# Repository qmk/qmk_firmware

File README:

To build:

make iris/rev2:pogues_uk

to then install:

make iris/rev2:pogues_uk:avrdude

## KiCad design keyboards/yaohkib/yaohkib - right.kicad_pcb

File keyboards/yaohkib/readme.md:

# YAOHKIB
A custom 42 Key Keyboard.
> - stick out thumb cluster.
> - multiple aux socket locations.
> - 128x64 OLED and 128x32 OLED Support

Keyboard Maintainer: [jabbato](https://github.com/jabbato/)  
Hardware Supported: Pro Micro, 128x64/128x32 OLED
Hardware Availability: [PCB & Case Data](https://github.com/jabbato/yaohkib)

Make example:

```sh
make yaohkib:default
```

See the [build environment setup](https://docs.qmk.fm/#/getting_started_build_tools) and the [make instructions](https://docs.qmk.fm/#/getting_started_make_guide) for more information. Brand new to QMK? Start with our [Complete Newbs Guide](https://docs.qmk.fm/#/newbs).

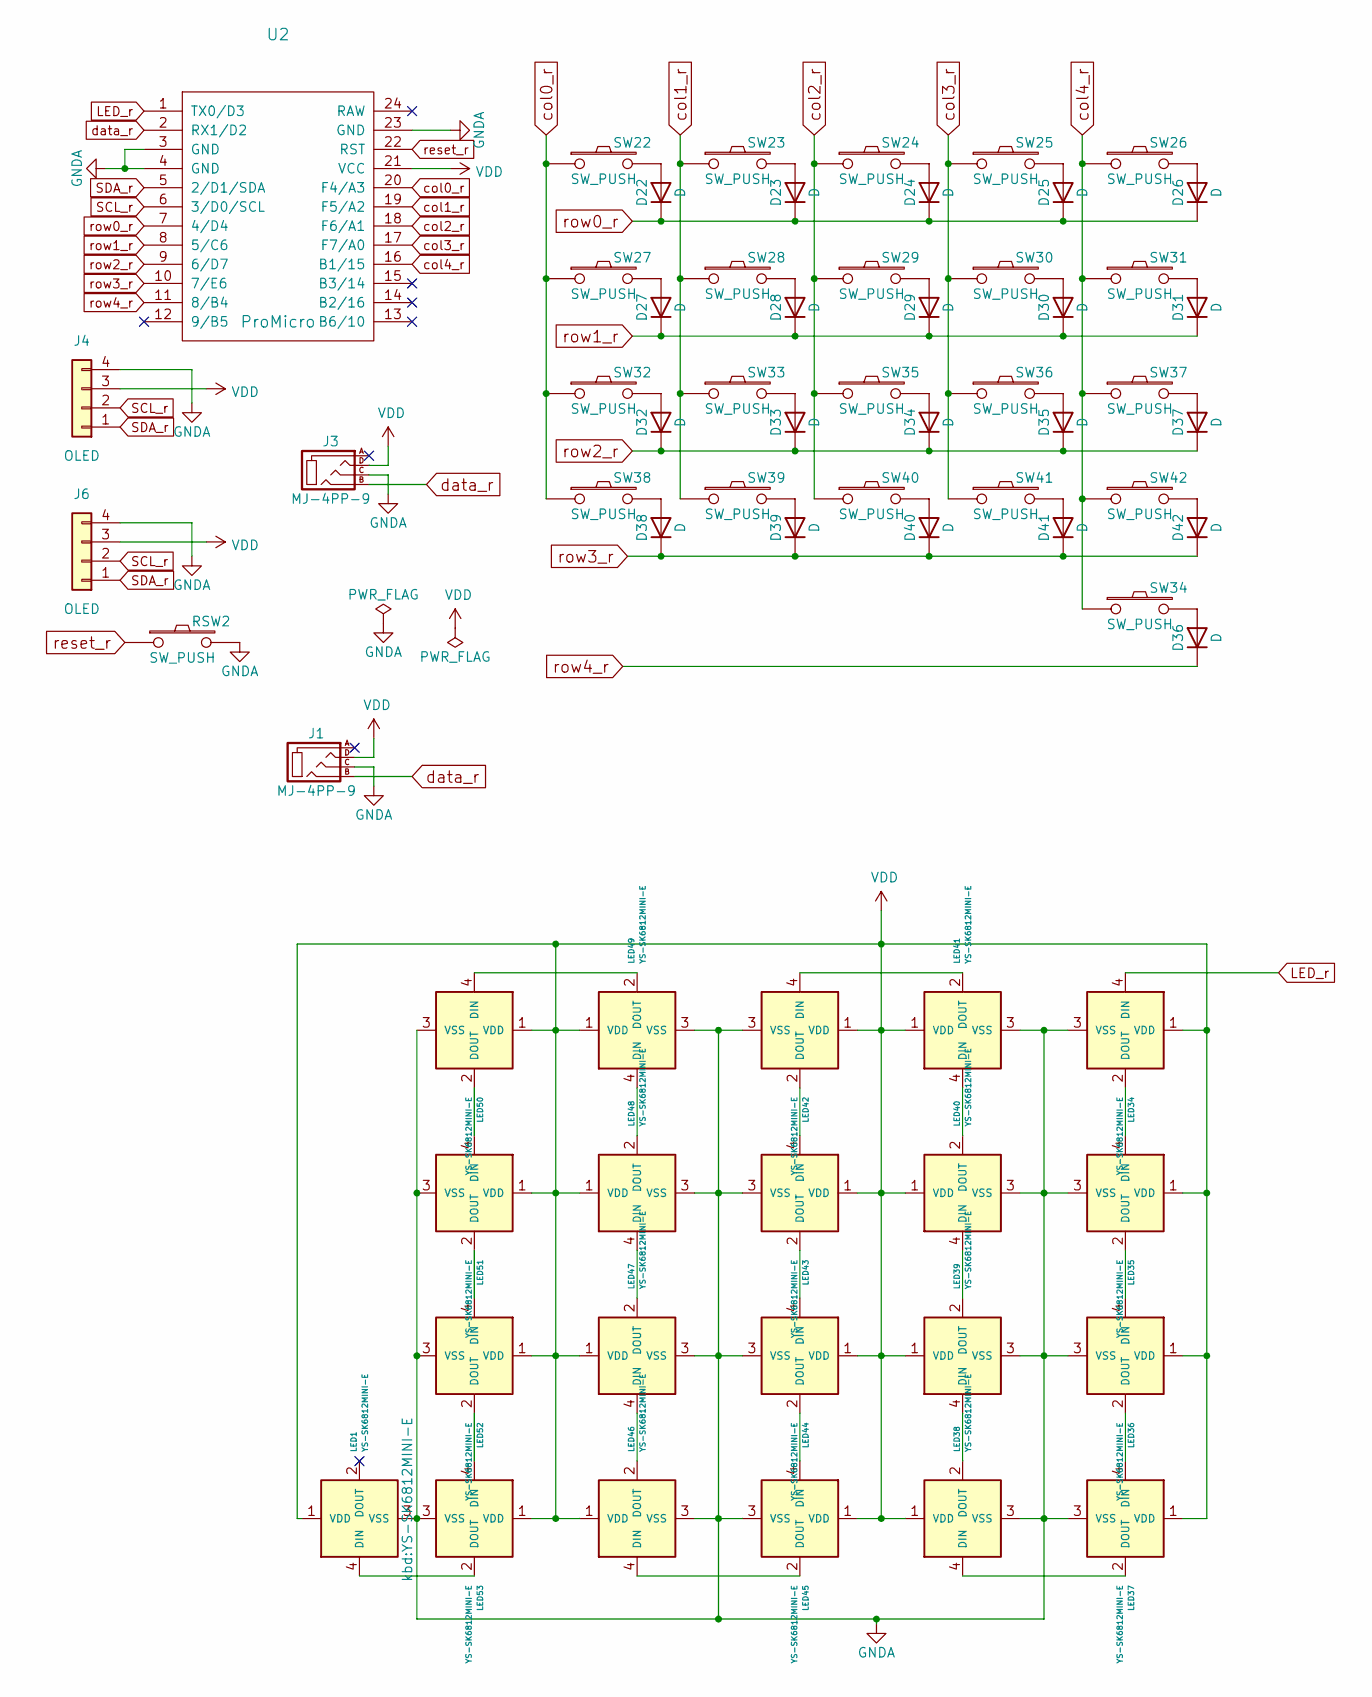
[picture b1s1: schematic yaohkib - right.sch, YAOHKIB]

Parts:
D22, D23, D24, D25, D26, D27, D28, D29, D30, D31, D32, D33, D34, D35, D36, D37, D38, D39, D40, D41, D42: D; D3_SMD_v2
J1, J3: MJ-4PP-9; MJ-4PP-9_1side
J4, J6: OLED; OLED_1side
LED1, LED34, LED35, LED36, LED37, LED38, LED39, LED40, LED41, LED42, LED43, LED44, LED45, LED46, LED47, LED48, LED49, LED50, LED51, LED52, LED53: YS-SK6812MINI-E
RSW2: SW_PUSH; ResetSW_1side
SW22, SW23, SW24, SW25, SW26, SW27, SW28, SW29, SW30, SW31, SW32, SW33, SW35, SW36, SW37, SW38, SW39, SW40: SW_PUSH; CherryMX_Hotswap
SW34, SW41, SW42: SW_PUSH; CherryMX_Hotswap_1.5u
U2: ProMicro; ProMicro_v3

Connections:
GNDA: J1.C, J3.C, J4.4, J6.4, LED1.3 (VSS), LED34.3 (VSS), LED35.3 (VSS), LED36.3 (VSS), LED37.3 (VSS), LED38.3 (VSS), LED39.3 (VSS), LED40.3 (VSS), LED41.3 (VSS), LED42.3 (VSS), LED43.3 (VSS), LED44.3 (VSS), LED45.3 (VSS), LED46.3 (VSS), LED47.3 (VSS), LED48.3 (VSS), LED49.3 (VSS), LED50.3 (VSS), LED51.3 (VSS), LED52.3 (VSS), LED53.3 (VSS), RSW2.2, U2.3 (GND), U2.4 (GND), U2.23 (GND)
LED_r: LED34.4 (DIN), U2.1 (TX0/D3)
unnamed: D22.2 (A), SW22.2
unnamed: D23.2 (A), SW23.2
unnamed: D24.2 (A), SW24.2
unnamed: D25.2 (A), SW25.2
unnamed: D26.2 (A), SW26.2
unnamed: D27.2 (A), SW27.2
unnamed: D28.2 (A), SW28.2
unnamed: D29.2 (A), SW29.2
unnamed: D30.2 (A), SW30.2
unnamed: D31.2 (A), SW31.2
unnamed: D32.2 (A), SW32.2
unnamed: D33.2 (A), SW33.2
unnamed: D34.2 (A), SW35.2
unnamed: D35.2 (A), SW36.2
unnamed: D36.2 (A), SW34.2
unnamed: D37.2 (A), SW37.2
unnamed: D38.2 (A), SW38.2
unnamed: D39.2 (A), SW39.2
unnamed: D40.2 (A), SW40.2
unnamed: D41.2 (A), SW41.2
unnamed: D42.2 (A), SW42.2
unnamed: LED1.4 (DIN), LED53.2 (DOUT)
unnamed: LED34.2 (DOUT), LED35.4 (DIN)
unnamed: LED35.2 (DOUT), LED36.4 (DIN)
unnamed: LED36.2 (DOUT), LED37.4 (DIN)
unnamed: LED37.2 (DOUT), LED38.4 (DIN)
unnamed: LED38.2 (DOUT), LED39.4 (DIN)
unnamed: LED39.2 (DOUT), LED40.4 (DIN)
unnamed: LED40.2 (DOUT), LED41.4 (DIN)
unnamed: LED41.2 (DOUT), LED42.4 (DIN)
unnamed: LED42.2 (DOUT), LED43.4 (DIN)
unnamed: LED43.2 (DOUT), LED44.4 (DIN)
unnamed: LED44.2 (DOUT), LED45.4 (DIN)
unnamed: LED45.2 (DOUT), LED46.4 (DIN)
unnamed: LED46.2 (DOUT), LED47.4 (DIN)
unnamed: LED47.2 (DOUT), LED48.4 (DIN)
unnamed: LED48.2 (DOUT), LED49.4 (DIN)
unnamed: LED49.2 (DOUT), LED50.4 (DIN)
unnamed: LED50.2 (DOUT), LED51.4 (DIN)
unnamed: LED51.2 (DOUT), LED52.4 (DIN)
unnamed: LED52.2 (DOUT), LED53.4 (DIN)
SCL_r: J4.2, J6.2, U2.6 (3/D0/SCL)
SDA_r: J4.1, J6.1, U2.5 (2/D1/SDA)
VDD: J1.D, J3.D, J4.3, J6.3, LED1.1 (VDD), LED34.1 (VDD), LED35.1 (VDD), LED36.1 (VDD), LED37.1 (VDD), LED38.1 (VDD), LED39.1 (VDD), LED40.1 (VDD), LED41.1 (VDD), LED42.1 (VDD), LED43.1 (VDD), LED44.1 (VDD), LED45.1 (VDD), LED46.1 (VDD), LED47.1 (VDD), LED48.1 (VDD), LED49.1 (VDD), LED50.1 (VDD), LED51.1 (VDD), LED52.1 (VDD), LED53.1 (VDD), U2.21 (VCC)
col0_r: SW22.1, SW27.1, SW32.1, SW38.1, U2.20 (F4/A3)
col1_r: SW23.1, SW28.1, SW33.1, SW39.1, U2.19 (F5/A2)
col2_r: SW24.1, SW29.1, SW35.1, SW40.1, U2.18 (F6/A1)
col3_r: SW25.1, SW30.1, SW36.1, SW41.1, U2.17 (F7/A0)
col4_r: SW26.1, SW31.1, SW34.1, SW37.1, SW42.1, U2.16 (B1/15)
data_r: J1.B, J3.B, U2.2 (RX1/D2)
reset_r: RSW2.1, U2.22 (RST)
row0_r: D22.1 (K), D23.1 (K), D24.1 (K), D25.1 (K), D26.1 (K), U2.7 (4/D4)
row1_r: D27.1 (K), D28.1 (K), D29.1 (K), D30.1 (K), D31.1 (K), U2.8 (5/C6)
row2_r: D32.1 (K), D33.1 (K), D34.1 (K), D35.1 (K), D37.1 (K), U2.9 (6/D7)
row3_r: D38.1 (K), D39.1 (K), D40.1 (K), D41.1 (K), D42.1 (K), U2.10 (7/E6)
row4_r: D36.1 (K), U2.11 (8/B4)

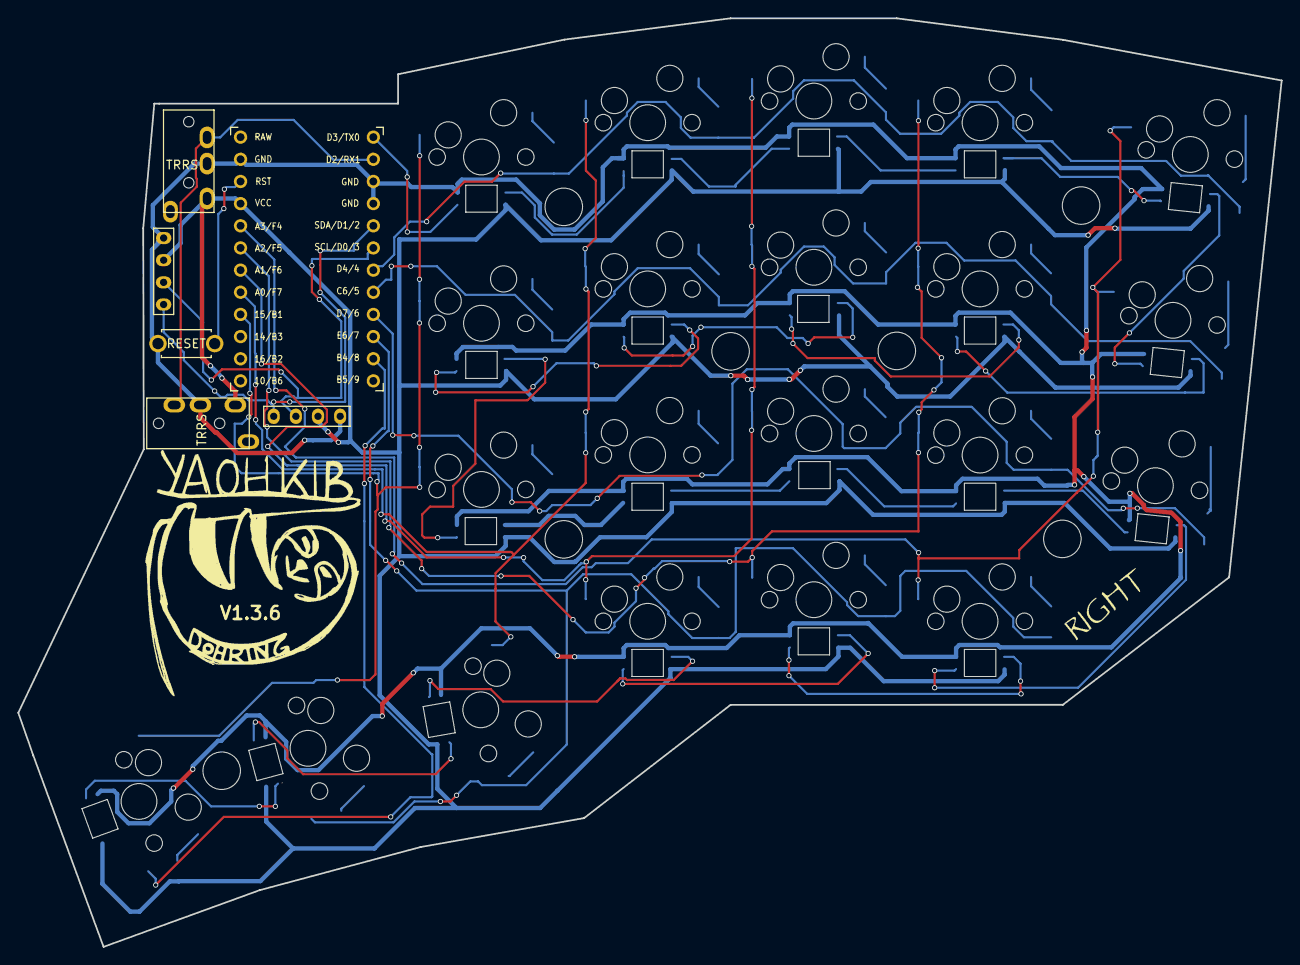
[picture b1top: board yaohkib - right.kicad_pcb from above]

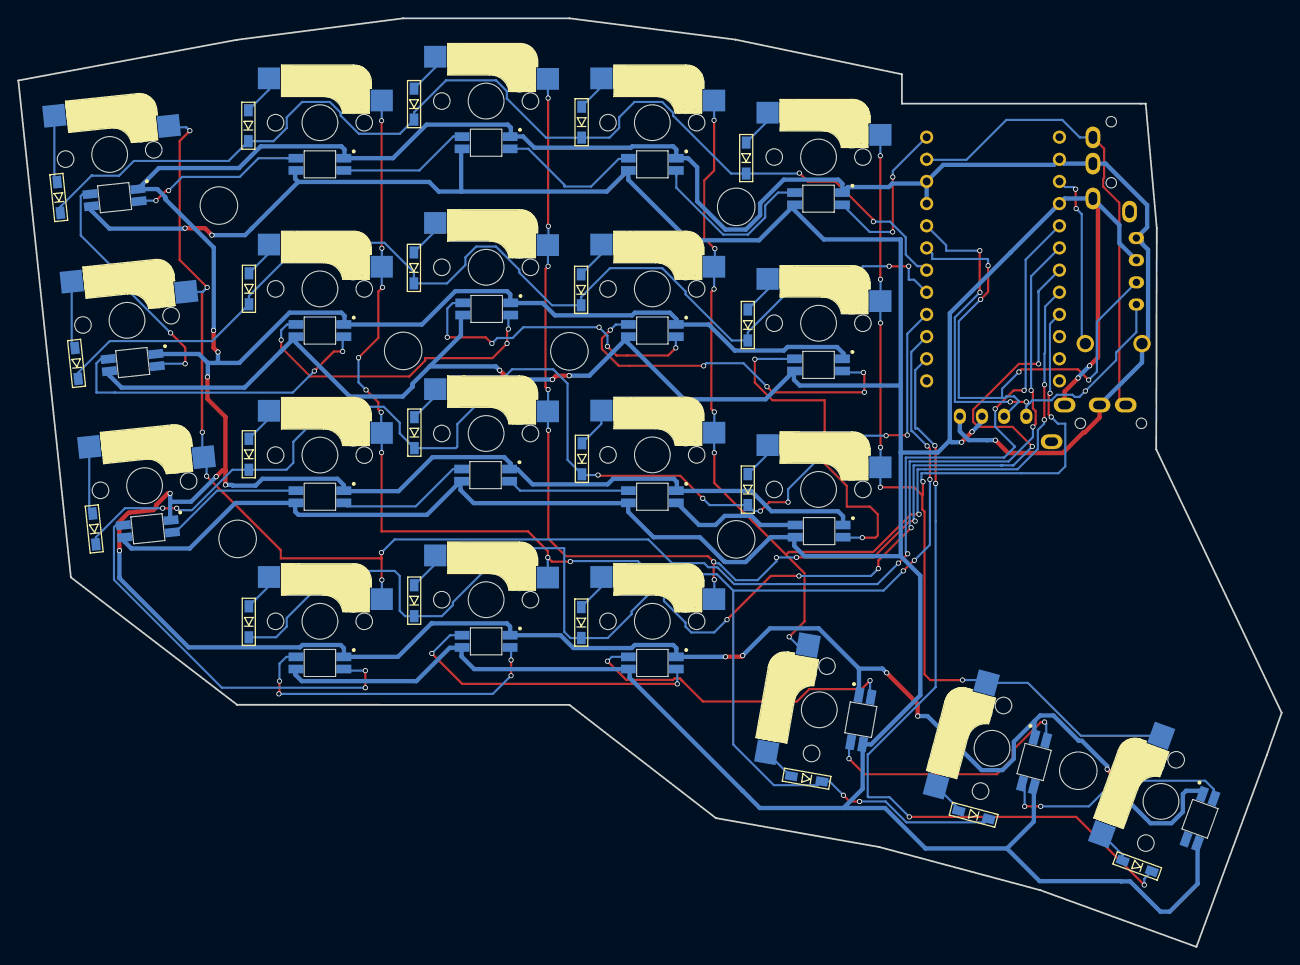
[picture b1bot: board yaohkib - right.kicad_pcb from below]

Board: 2 copper layers, 144.8 x 106.4 mm, 76 parts (49 on the bottom side), 58 nets.

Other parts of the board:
Ref**: Val**; M2_HOLE_v2
Ref**#2, Ref**#3, Ref**#4, Ref**#5, Ref**#6, Ref**#7: Val**; M2_HOLE_v2

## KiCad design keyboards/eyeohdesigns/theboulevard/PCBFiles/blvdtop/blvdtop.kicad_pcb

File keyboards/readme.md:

# 1x5stick

*A short description of the keyboard/project*

* Keyboard Maintainer: [LakesideMiners](https://github.com/LakesideMiners)
* Hardware Supported: *The PCBs, controllers supported*
* Hardware Availability: *Links to where you can find this hardware*

Make example for this keyboard (after setting up your build environment):

    make 1x5stick:default

Flashing example for this keyboard:

    make 1x5stick:default:flash

See the [build environment setup](https://docs.qmk.fm/#/getting_started_build_tools) and the [make instructions](https://docs.qmk.fm/#/getting_started_make_guide) for more information. Brand new to QMK? Start with our [Complete Newbs Guide](https://docs.qmk.fm/#/newbs).

## Bootloader

Enter the bootloader in 3 ways:

* **Bootmagic reset**: Hold down the key at (0,0) in the matrix (usually the top left key or Escape) and plug in the keyboard
* **Physical reset button**: Briefly press the button on the back of the PCB - some may have pads you must short instead
* **Keycode in layout**: Press the key mapped to `QK_BOOT` if it is available

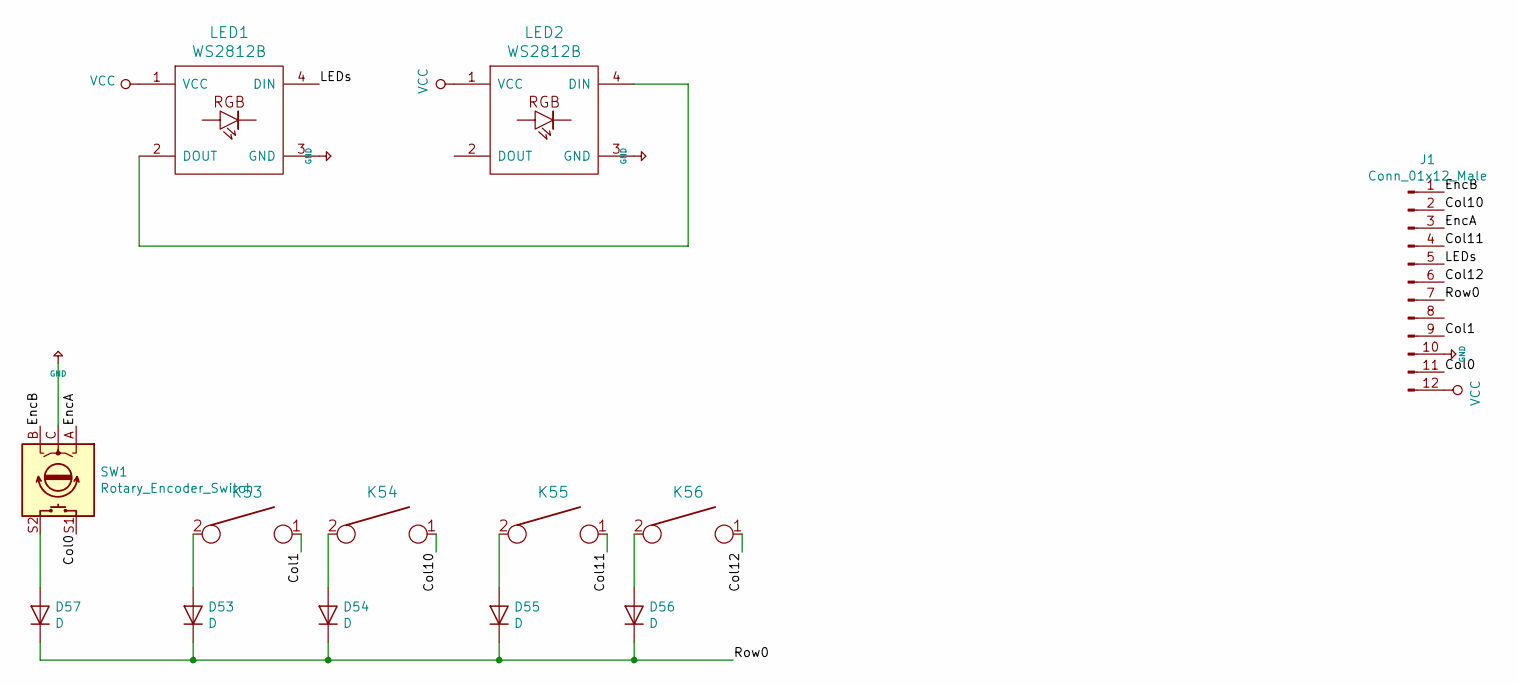
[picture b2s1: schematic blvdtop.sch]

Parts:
D53, D54, D55, D56, D57: D; D_SOD123
J1: Conn_01x12_Male; PinHeader_2x06_P2.00mm_Vertical
K53, K54, K55, K56: KEYSW; SW_Cherry_MX_1.00u_PCB_No_Silk
LED1, LED2: WS2812B; LED_D5.0mm-4_RGB
SW1: Rotary_Encoder_Switch; RotaryEncoder_Alps_EC11E-Switch_Vertical_H20mm

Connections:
+5V: J1.10, LED1.3 (GND), LED2.3 (GND), SW1.C
/Col0: J1.11, SW1.S1
/Col1: J1.9, K53.1
/Col10: J1.2, K54.1
/Col11: J1.4, K55.1
/Col12: J1.6, K56.1
/EncA: J1.3, SW1.A
/EncB: J1.1, SW1.B
/LEDs: J1.5, LED1.4 (DIN)
/Row0: D53.1 (K), D54.1 (K), D55.1 (K), D56.1 (K), D57.1 (K), J1.7
unnamed: D53.2 (A), K53.2
unnamed: D54.2 (A), K54.2
unnamed: D55.2 (A), K55.2
unnamed: D56.2 (A), K56.2
unnamed: D57.2 (A), SW1.S2
unnamed: LED1.2 (DOUT), LED2.4 (DIN)
VCC: J1.12, LED1.1 (VCC), LED2.1 (VCC)

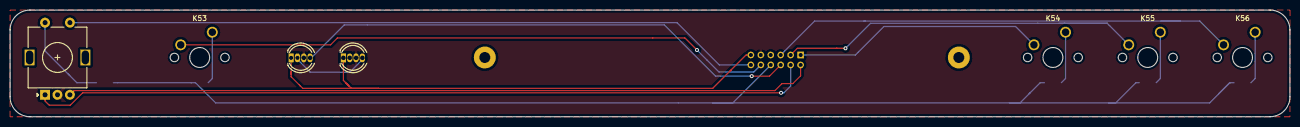
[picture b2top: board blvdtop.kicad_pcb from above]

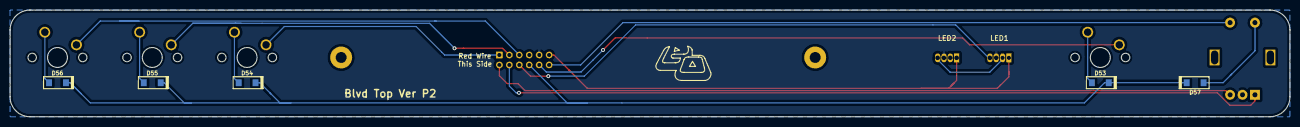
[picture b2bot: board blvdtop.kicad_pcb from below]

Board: 2 copper layers, 257.2 x 21.4 mm, 13 parts (6 on the bottom side), 17 nets.

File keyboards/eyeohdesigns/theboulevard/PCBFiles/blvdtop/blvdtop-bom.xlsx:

Item | Designator | Manufacturer Part Number | Quantity | Store | Desc | Package
1 | D53, D54, D55, D56, D57 | 1N4148W-7-F | 5 | LCSC | D | SOD-123
2 | J1 | PZ200V-12-12P | 1 | LCSC |  | 2x6 2.00mm pitch
3 | LED1, LED2 |  | 2 |  | WS2812B | 4 pin through hole
4 | SW1 |  | 1 | LCSC | Encoder with switch | EC11

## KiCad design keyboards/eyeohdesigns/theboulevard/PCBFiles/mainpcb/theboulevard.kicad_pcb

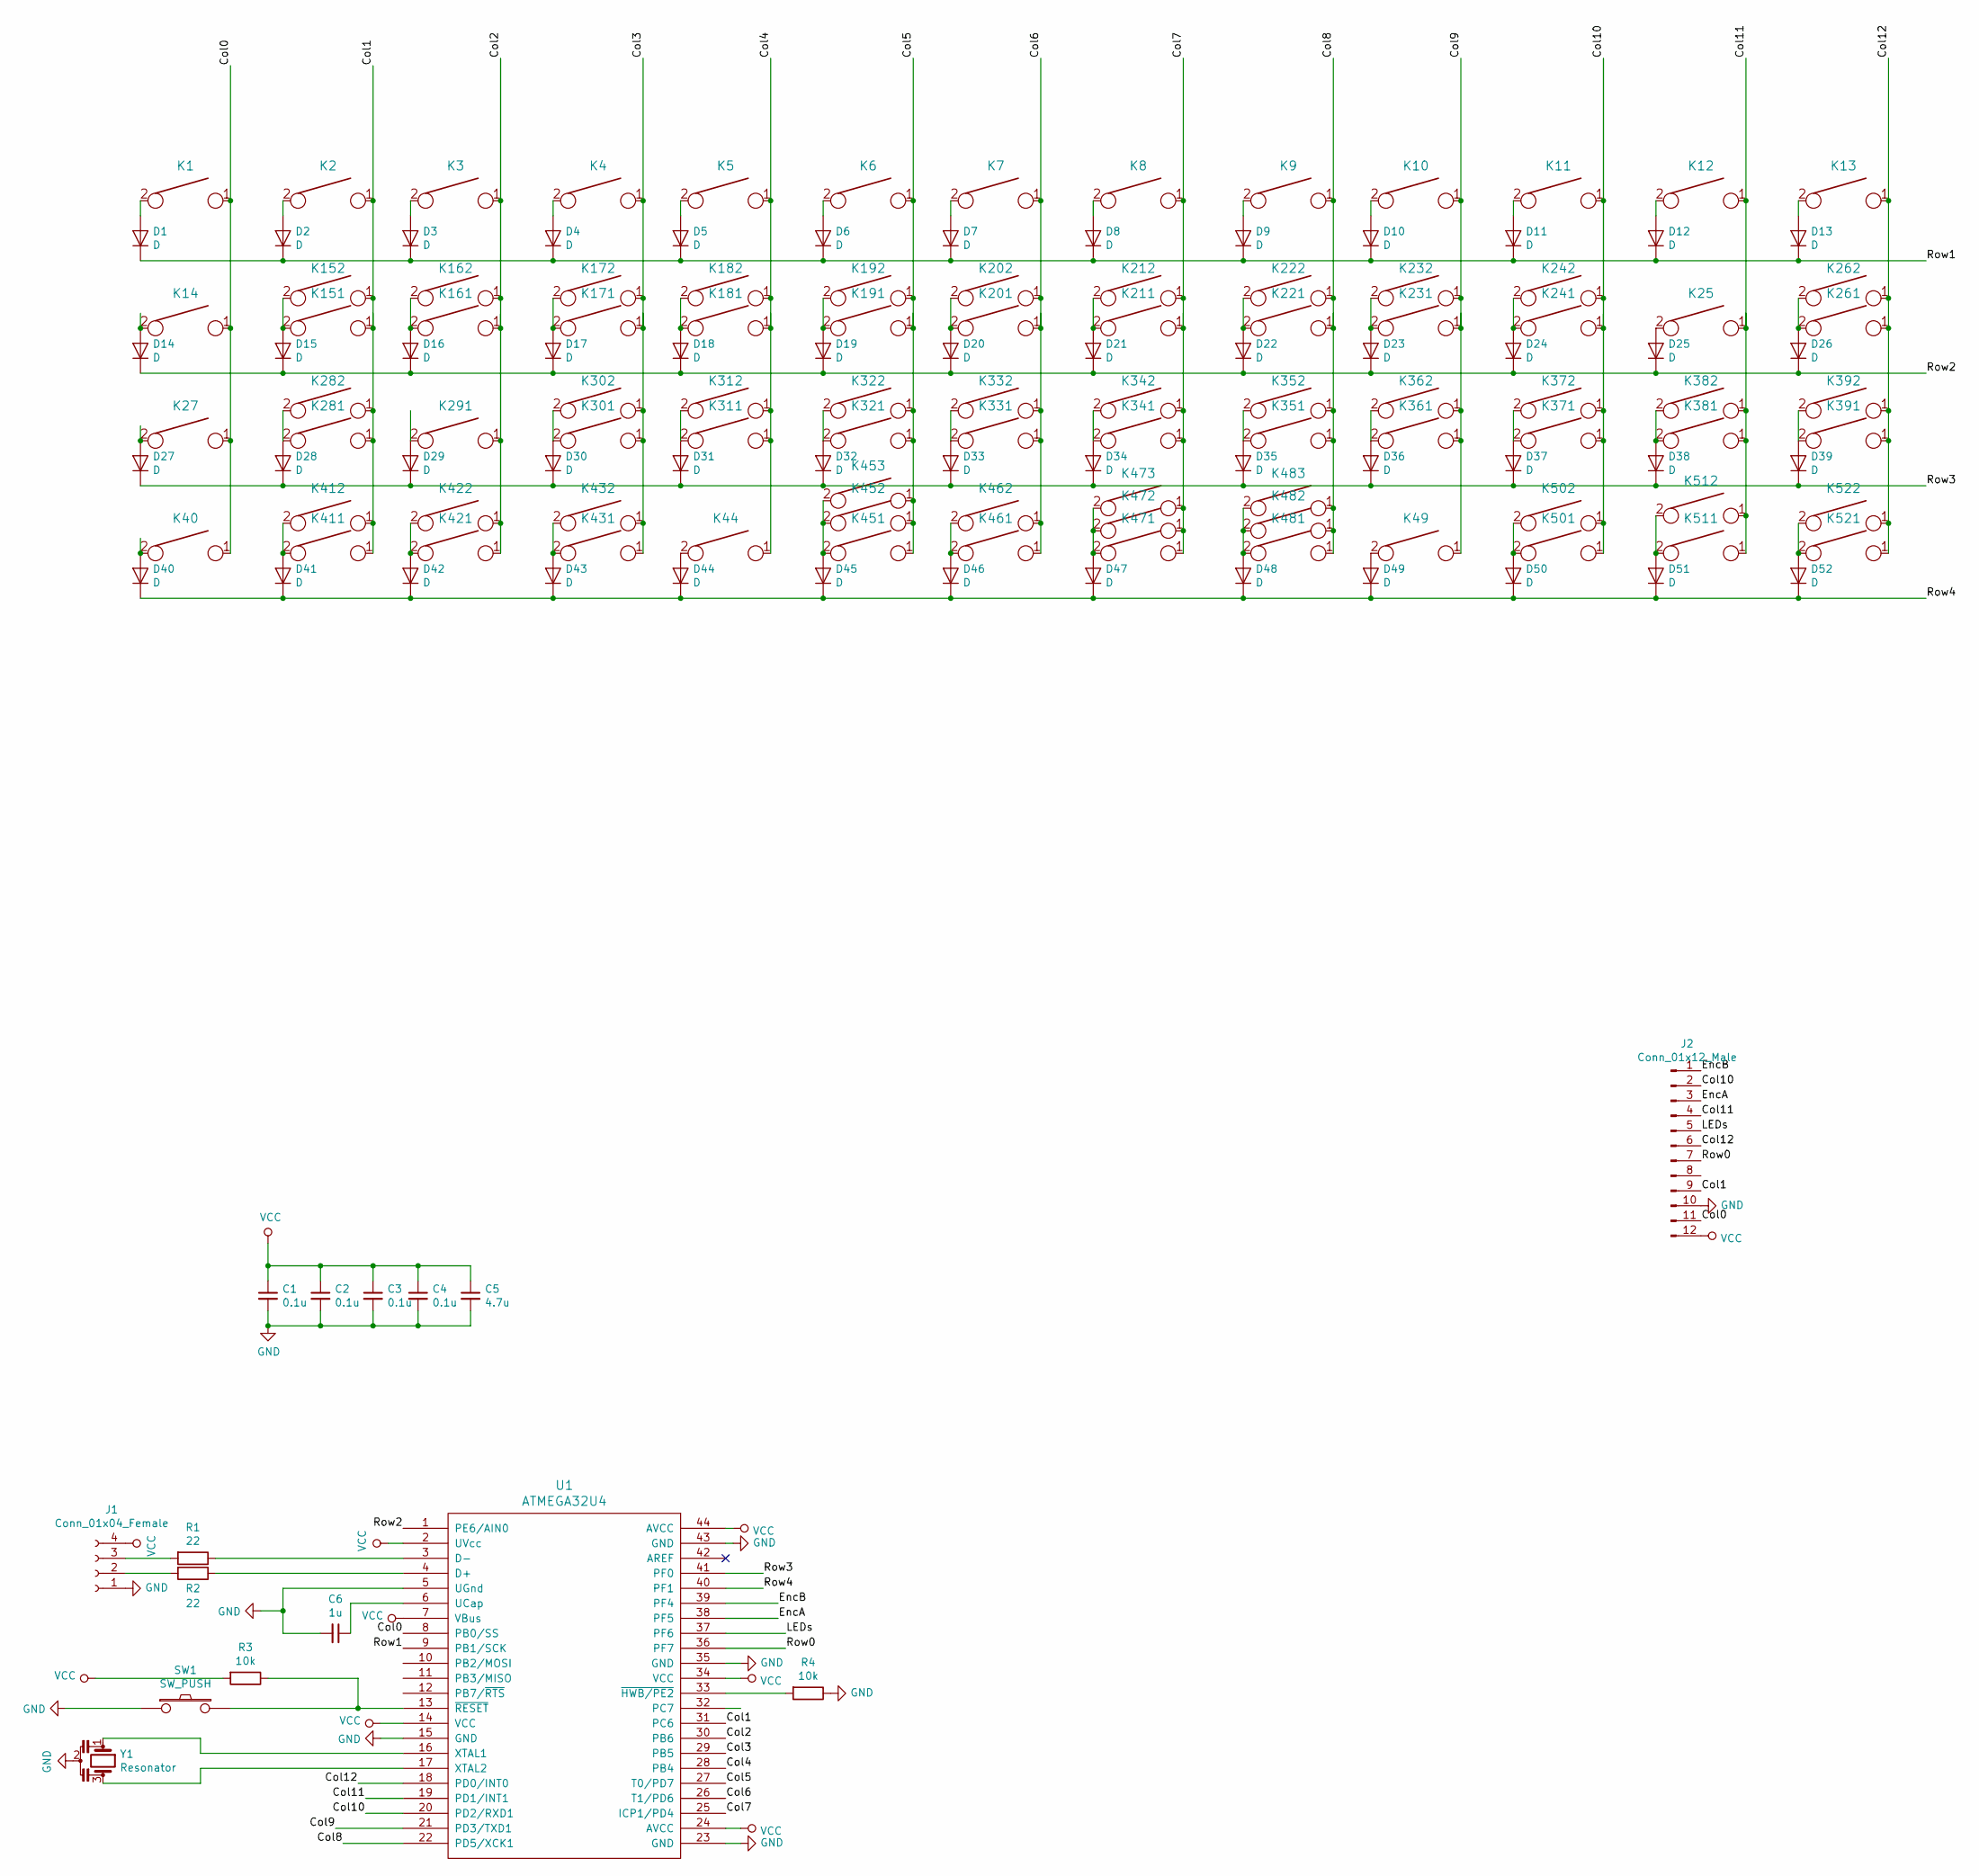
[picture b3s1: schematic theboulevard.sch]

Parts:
C1, C2, C3, C4: 0.1u; C_0603_1608Metric_Pad1.05x0.95mm_HandSolder
C5: 4.7u; C_0603_1608Metric_Pad1.05x0.95mm_HandSolder
C6: 1u; C_0603_1608Metric_Pad1.05x0.95mm_HandSolder
D1, D2, D3, D4, D5, D6, D7, D8, D9, D10, D11, D12, D13, D14, D15, D16, D17, D18, D19, D20, D21, D22, D23, D24, D25, D26, D27, D28, D29, D30, D31, D32, D33, D34, D35, D36, D37, D38, D39, D40, D41, D42, D43, D44, D45, D46, D47, D48, D49, D50, D51, D52: D; D_SOD123
J1: Conn_01x04_Female; JST_SH_SM04B-SRSS-TB_1x04-1MP_P1.00mm_Horizontal
J2: Conn_01x12_Male; PinHeader_2x06_P2.00mm_Horizontal
K1, K2, K3, K4, K5, K6, K7, K8, K9, K10, K11, K12, K13, K14, K25, K27, K40, K44, K49, K151, K161, K162, K171, K172, K181, K182, K191, K192, K201, K202, K211, K212, K221, K222, K231, K232, K241, K242, K261, K281, K291, K301, K302, K311, K312, K321, K322, K331, K332, K341, K342, K351, K352, K361, K362, K371, K372, K381, K382, K391, K411, K421, K431, K451, K461, K471, K481, K501, K511, K521: KEYSW; SW_Cherry_MX_1.00u_PCB_No_Silk
K152, K392, K412, K432, K502, K522: KEYSW; SW_Cherry_MX_1.25u_PCB_No_Silk
K262, K282: KEYSW; SW_Cherry_MX_1.75u_PCB_No_Silk
K422, K512: KEYSW; SW_Cherry_MX_1.50u_PCB_No_Silk
K452, K473, K483: KEYSW; SW_Cherry_MX_2.00u_PCB_Flip_Stab
K453: KEYSW; MX_2.75u_PCB_No_Silk_Flipped_Stab
K462: KEYSW; MX_6.25u_PCB_Flipped_Stab_No_Silk
K472: KEYSW; SW_Cherry_MX_7u_PCB_No_Silk_Flip_Stab
K482: KEYSW; MX_2.25u_PCB_No_Silk_Flipped_Stab
R1, R2: 22; R_0603_1608Metric_Pad1.05x0.95mm_HandSolder
R3, R4: 10k; R_0603_1608Metric_Pad1.05x0.95mm_HandSolder
SW1: SW_PUSH; SW_SPST_TL3342
U1: ATMEGA32U4; QFN-44-1EP_7x7mm_P0.5mm_EP5.2x5.2mm
Y1: Resonator; Abracon_Resonator_16MHz_22pf

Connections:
/Col0: J2.11, K1.1, K14.1, K27.1, K40.1, U1.8 (PB0/SS)
/Col1: J2.9, K2.1, K151.1, K152.1, K281.1, K282.1, K411.1, K412.1, U1.31 (PC6)
/Col2: K3.1, K161.1, K162.1, K291.1, K421.1, K422.1, U1.30 (PB6)
/Col3: K4.1, K171.1, K172.1, K301.1, K302.1, K431.1, K432.1, U1.29 (PB5)
/Col4: K5.1, K44.1, K181.1, K182.1, K311.1, K312.1, U1.28 (PB4)
/Col5: K6.1, K191.1, K192.1, K321.1, K322.1, K451.1, K452.1, K453.1, U1.27 (T0/PD7)
/Col6: K7.1, K201.1, K202.1, K331.1, K332.1, K461.1, K462.1, U1.26 (T1/PD6)
/Col7: K8.1, K211.1, K212.1, K341.1, K342.1, K471.1, K472.1, K473.1, U1.25 (ICP1/PD4)
/Col8: K9.1, K221.1, K222.1, K351.1, K352.1, K481.1, K482.1, K483.1, U1.22 (PD5/XCK1)
/Col9: K10.1, K49.1, K231.1, K232.1, K361.1, K362.1, U1.21 (PD3/TXD1)
/Col10: J2.2, K11.1, K241.1, K242.1, K371.1, K372.1, K501.1, K502.1, U1.20 (PD2/RXD1)
/Col11: J2.4, K12.1, K25.1, K381.1, K382.1, K511.1, K512.1, U1.19 (PD1/INT1)
/Col12: J2.6, K13.1, K261.1, K262.1, K391.1, K392.1, K521.1, K522.1, U1.18 (PD0/INT0)
/EncA: J2.3, U1.38 (PF5)
/EncB: J2.1, U1.39 (PF4)
/LEDs: J2.5, U1.37 (PF6)
/Row0: J2.7, U1.36 (PF7)
/Row1: D1.1 (K), D2.1 (K), D3.1 (K), D4.1 (K), D5.1 (K), D6.1 (K), D7.1 (K), D8.1 (K), D9.1 (K), D10.1 (K), D11.1 (K), D12.1 (K), D13.1 (K), U1.9 (PB1/SCK)
/Row2: D14.1 (K), D15.1 (K), D16.1 (K), D17.1 (K), D18.1 (K), D19.1 (K), D20.1 (K), D21.1 (K), D22.1 (K), D23.1 (K), D24.1 (K), D25.1 (K), D26.1 (K), U1.1 (PE6/AIN0)
/Row3: D27.1 (K), D28.1 (K), D29.1 (K), D30.1 (K), D31.1 (K), D32.1 (K), D33.1 (K), D34.1 (K), D35.1 (K), D36.1 (K), D37.1 (K), D38.1 (K), D39.1 (K), U1.41 (PF0)
/Row4: D40.1 (K), D41.1 (K), D42.1 (K), D43.1 (K), D44.1 (K), D45.1 (K), D46.1 (K), D47.1 (K), D48.1 (K), D49.1 (K), D50.1 (K), D51.1 (K), D52.1 (K), U1.40 (PF1)
GND: C1.2, C2.2, C3.2, C4.2, C5.2, C6.2, J1.1, J2.10, R4.1, SW1.1, U1.5 (UGnd), U1.15 (GND), U1.23 (GND), U1.35 (GND), U1.43 (GND), Y1.2
unnamed: C6.1, U1.6 (UCap)
unnamed: D1.2 (A), K1.2
unnamed: D2.2 (A), K2.2
unnamed: D3.2 (A), K3.2
unnamed: D4.2 (A), K4.2
unnamed: D5.2 (A), K5.2
unnamed: D6.2 (A), K6.2
unnamed: D7.2 (A), K7.2
unnamed: D8.2 (A), K8.2
unnamed: D9.2 (A), K9.2
unnamed: D10.2 (A), K10.2
unnamed: D11.2 (A), K11.2
unnamed: D12.2 (A), K12.2
unnamed: D13.2 (A), K13.2
unnamed: D14.2 (A), K14.2
unnamed: D15.2 (A), K151.2, K152.2
unnamed: D16.2 (A), K161.2, K162.2
unnamed: D17.2 (A), K171.2, K172.2
unnamed: D18.2 (A), K181.2, K182.2
unnamed: D19.2 (A), K191.2, K192.2
unnamed: D20.2 (A), K201.2, K202.2
unnamed: D21.2 (A), K211.2, K212.2
unnamed: D22.2 (A), K221.2, K222.2
unnamed: D23.2 (A), K231.2, K232.2
unnamed: D24.2 (A), K241.2, K242.2
unnamed: D25.2 (A), K25.2
unnamed: D26.2 (A), K261.2, K262.2
unnamed: D27.2 (A), K27.2
unnamed: D28.2 (A), K281.2, K282.2
unnamed: D29.2 (A), K291.2
unnamed: D30.2 (A), K301.2, K302.2
unnamed: D31.2 (A), K311.2, K312.2
unnamed: D32.2 (A), K321.2, K322.2
unnamed: D33.2 (A), K331.2, K332.2
unnamed: D34.2 (A), K341.2, K342.2
unnamed: D35.2 (A), K351.2, K352.2
unnamed: D36.2 (A), K361.2, K362.2
unnamed: D37.2 (A), K371.2, K372.2
unnamed: D38.2 (A), K381.2, K382.2
unnamed: D39.2 (A), K391.2, K392.2
unnamed: D40.2 (A), K40.2
unnamed: D41.2 (A), K411.2, K412.2
unnamed: D42.2 (A), K421.2, K422.2
unnamed: D43.2 (A), K431.2, K432.2
unnamed: D44.2 (A), K44.2
unnamed: D45.2 (A), K451.2, K452.2, K453.2
unnamed: D46.2 (A), K461.2, K462.2
unnamed: D47.2 (A), K471.2, K472.2, K473.2
unnamed: D48.2 (A), K481.2, K482.2, K483.2
unnamed: D49.2 (A), K49.2
unnamed: D50.2 (A), K501.2, K502.2
unnamed: D51.2 (A), K511.2, K512.2
unnamed: D52.2 (A), K521.2, K522.2
unnamed: J1.2, R2.2
unnamed: J1.3, R1.2
unnamed: R1.1, U1.3 (D-)
unnamed: R2.1, U1.4 (D+)
unnamed: R3.1, SW1.2, U1.13 (~RESET)
unnamed: R4.2, U1.33 (~HWB/PE2)
unnamed: U1.16 (XTAL1), Y1.1
unnamed: U1.17 (XTAL2), Y1.3
VCC: C1.1, C2.1, C3.1, C4.1, C5.1, J1.4, J2.12, R3.2, U1.2 (UVcc), U1.7 (VBus), U1.14 (VCC), U1.24 (AVCC), U1.34 (VCC), U1.44 (AVCC)

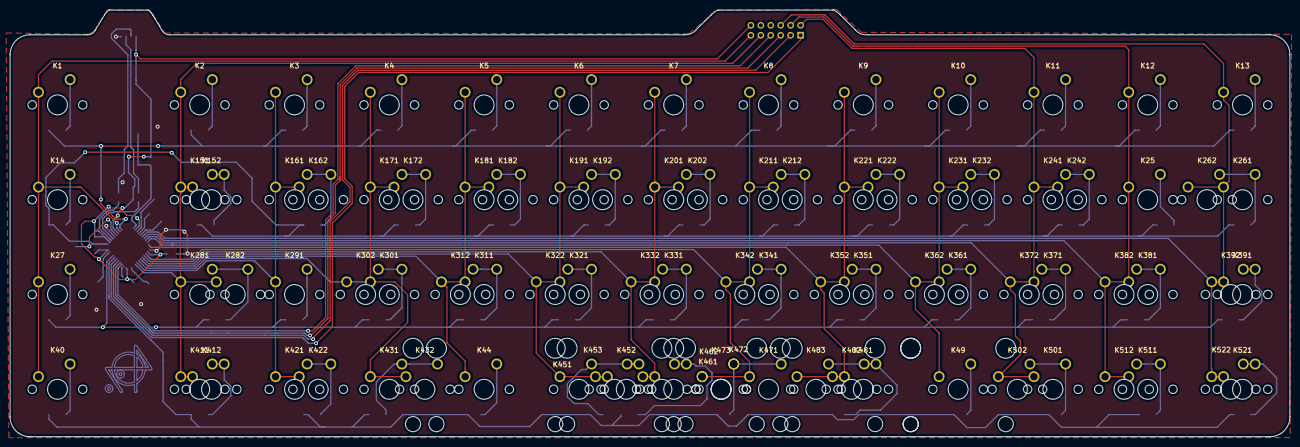
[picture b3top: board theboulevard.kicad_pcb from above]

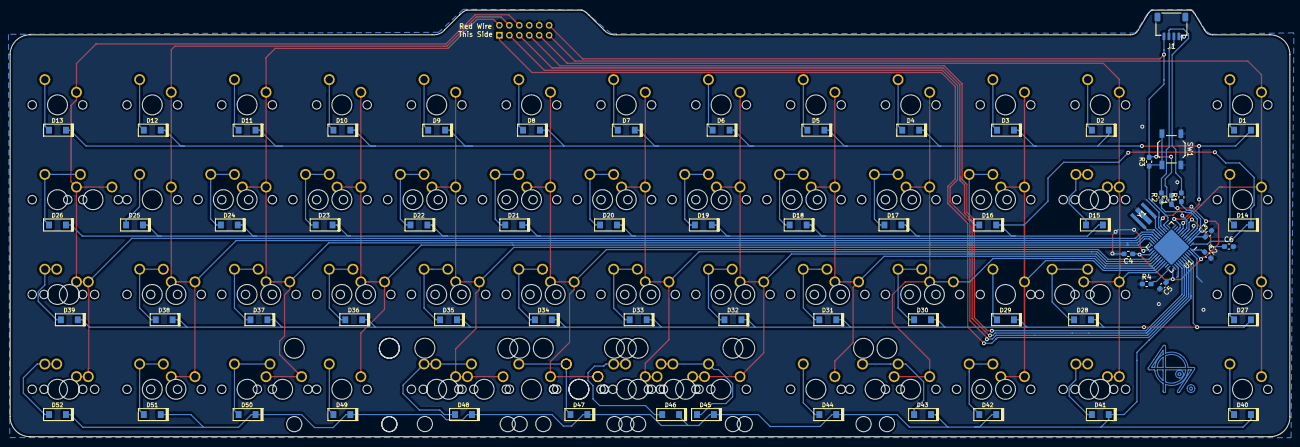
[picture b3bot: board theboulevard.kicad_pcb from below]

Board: 2 copper layers, 257.2 x 85.7 mm, 154 parts (67 on the bottom side), 84 nets.
